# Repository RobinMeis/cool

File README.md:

# cool
Attempt to make a stupid fridge-freezer a bit smarter and more energy efficient

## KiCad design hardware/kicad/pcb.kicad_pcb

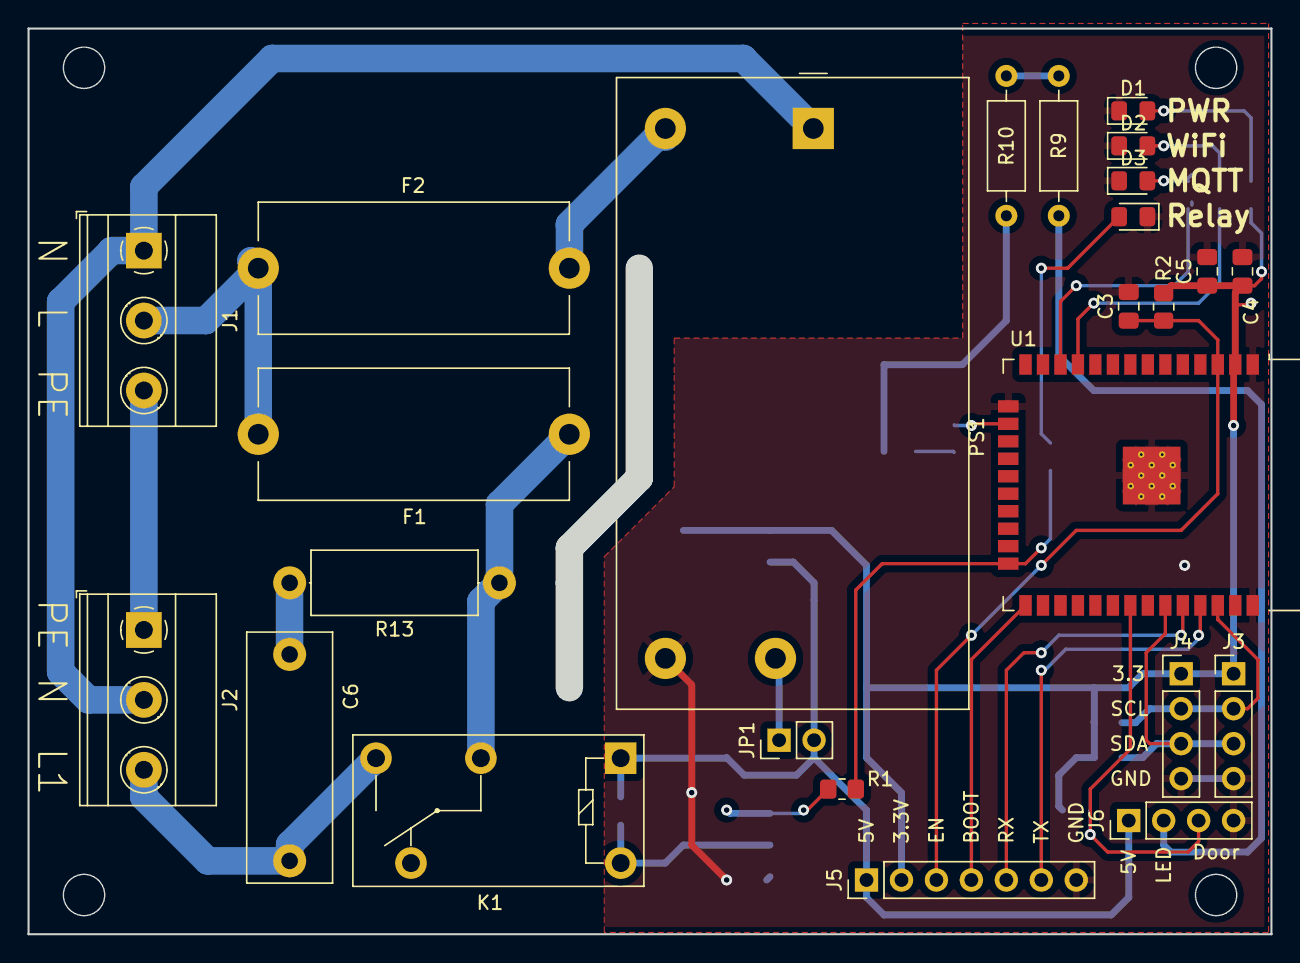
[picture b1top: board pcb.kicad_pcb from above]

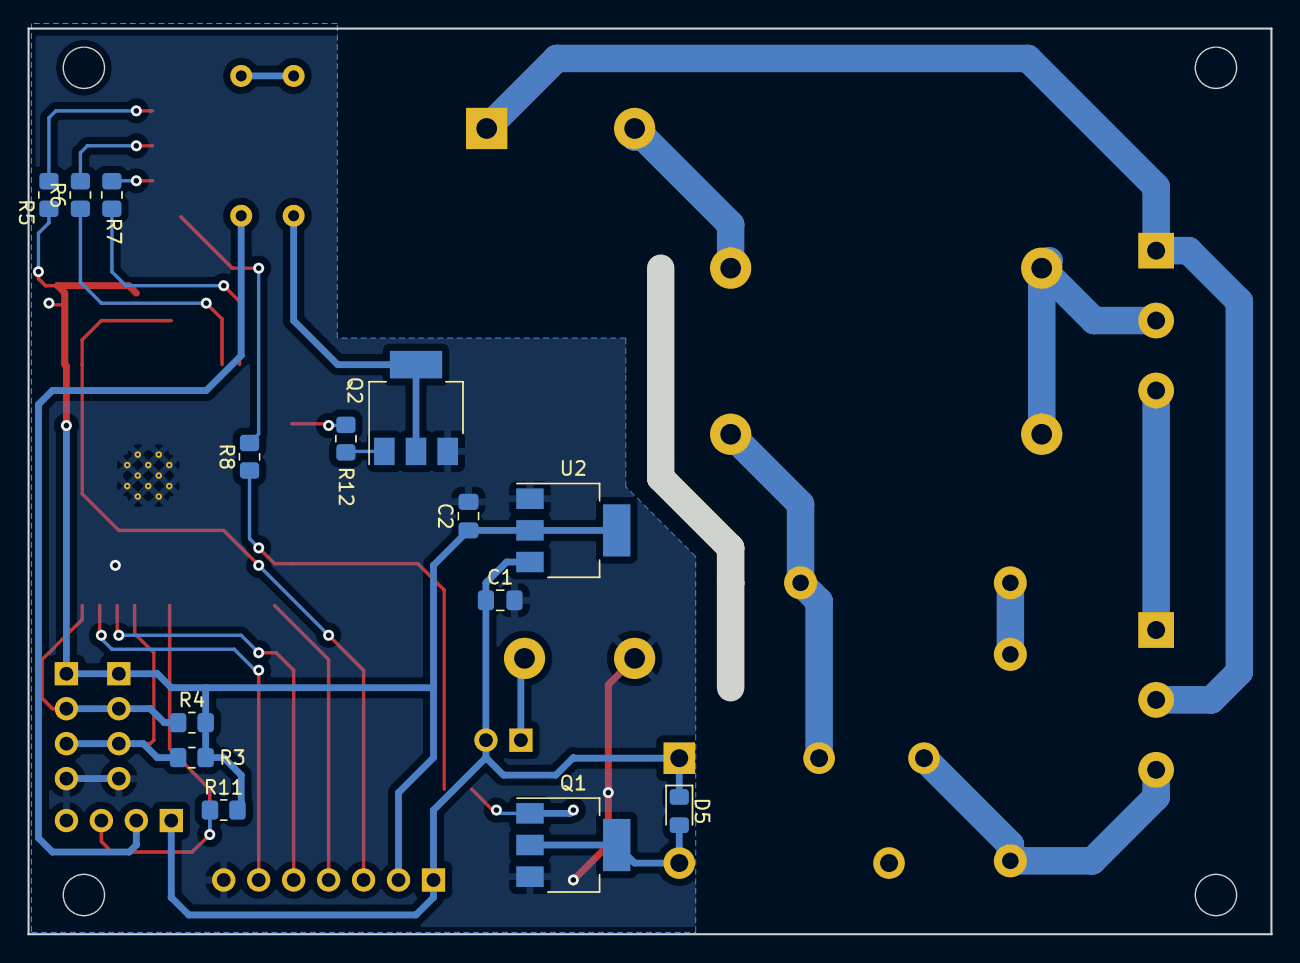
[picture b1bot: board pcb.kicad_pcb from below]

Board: 2 copper layers, 88.4 x 63.9 mm, 39 parts (14 on the bottom side), 32 nets.

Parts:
C1, C2: 22 uF; C_0805_2012Metric_Pad1.18x1.45mm_HandSolder
C3, C5: 100 nF; C_0805_2012Metric_Pad1.18x1.45mm_HandSolder
C4: 100 uF; C_0805_2012Metric_Pad1.18x1.45mm_HandSolder
C6: 100 nF; C_Rect_L18.0mm_W6.0mm_P15.00mm_FKS3_FKP3
D1, D2, D3, D4: LED; LED_0805_2012Metric_Pad1.15x1.40mm_HandSolder
D5: D; D_0805_2012Metric_Pad1.15x1.40mm_HandSolder
F1, F2: Fuse; Fuseholder_Cylinder-5x20mm_Stelvio-Kontek_PTF78_Horizontal_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
J1, J2: Screw_Terminal_01x03; TerminalBlock_Phoenix_MKDS-1,5-3-5.08_1x03_P5.08mm_Horizont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
J3, J4, J6: Conn_01x04_Male; PinHeader_1x04_P2.54mm_Vertical
J5: Conn_01x07_Male; PinHeader_1x07_P2.54mm_Vertical
JP1: Jumper_2_Bridged; PinHeader_1x02_P2.54mm_Vertical
K1: G5Q-1; Relay_SPDT_Omron-G5Q-1
PS1: IRM-05-5; Converter_ACDC_MeanWell_IRM-05-xx_THT
Q1, Q2: BCP56; SOT-223-3_TabPin2
R1, R5, R6, R7, R8, R12: 1k; R_0805_2012Metric_Pad1.20x1.40mm_HandSolder
R2, R3, R4, R11: 10k; R_0805_2012Metric_Pad1.20x1.40mm_HandSolder
R9, R10: 15; R_Axial_DIN0207_L6.3mm_D2.5mm_P10.16mm_Horizontal
R13: 220; R_Axial_DIN0414_L11.9mm_D4.5mm_P15.24mm_Horizontal
U1: ESP32-WROOM-32D; ESP32-WROOM-32
U2: AMS1117-3.3; SOT-223-3_TabPin2

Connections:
+3.3V: C2.1, C4.1, C5.1, J3.1, J4.1, J5.2, R2.2, R3.2, R4.2, R5.1, R11.2, U1.2 (VDD), U2.2 (VO)
+5V: C1.1, D5.1 (K), J5.1, J6.1, JP1.2 (B), K1.1, U2.3 (VI)
AC: F1.2, F2.1, J1.2
BOOT: J5.4, U1.25 (IO0)
Door: J6.3, R11.1, U1.31 (IO19)
EN: C3.1, J5.3, R2.1, U1.3 (EN)
Earth: J1.1, J2.2, PS1.1 (AC/N)
Earth_Protective: J1.3, J2.1
GND: C1.2, C2.2, C3.2, C4.2, C5.2, D1.1 (K), D2.1 (K), D3.1 (K), D4.1 (K), J3.4, J4.4, J5.7, J6.4, PS1.3 (-Vo), Q1.3 (E), Q2.3 (E), U1.1 (GND), U1.15 (GND), U1.38 (GND), U1.39 (GND), U2.1 (GND)
LED_MQTT: R7.1, U1.12 (IO27)
LED_WIFI: R6.1, U1.11 (IO26)
Light: Q2.2 (C), R10.2
unnamed: C6.1, R13.2
unnamed: C6.2, J2.3, K1.3
unnamed: D1.2 (A), R5.2
unnamed: D2.2 (A), R6.2
unnamed: D3.2 (A), R7.2
unnamed: D4.2 (A), R8.2
unnamed: D5.2 (A), K1.5, Q1.2 (C)
unnamed: F1.1, K1.2, R13.1
unnamed: F2.2, PS1.2 (AC/L)
unnamed: J6.2, R9.1
unnamed: JP1.1 (A), PS1.4 (+Vo)
unnamed: Q1.1 (B), R1.2
unnamed: Q2.1 (B), R12.2
unnamed: R9.2, R10.1
unnamed: R12.1, U1.16 (IO13)
RX: J5.5, U1.34 (RXD0/IO3)
Relay: R1.1, R8.1, U1.24 (IO2)
SCL: J3.2, J4.2, R4.1, U1.36 (IO22)
SDA: J3.3, J4.3, R3.1, U1.33 (IO21)
TX: J5.6, U1.35 (TXD0/IO1)

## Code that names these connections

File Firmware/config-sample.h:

#ifndef CONFIG_H
#define CONFIG_H

// Offset of temperature sensors
#define OFFSET_FRIDGE 0
#define OFFSET_FREEZER 0

// Wifi configuration
#define WIFI_SSID "IoT"
#define WIFI_PASSWORD "12345678"

// MQTT configuration
#define MQTT_SERVER "mqtt.local"
#define MQTT_PORT 1883
#define MQTT_CLIENT_ID host_name.c_str()
#define MQTT_USERNAME "user"
#define MQTT_PASSWORD "password"

// HTTP update server
#define HTTP_UPDATE_ENABLED true
#define HTTP_UPDATE_USERNAME "admin"
#define HTTP_UPDATE_PASSWORD "admin"

// Device type
#define HAS_FRIDGE true
#define HAS_FREEZER true

// Device name (autogenerated from device type)
#if HAS_FRIDGE==true
  #define DEVICE_NAME "Fridge"
#else
  #define DEVICE_NAME "Freezer"
#endif

// Pins
#define PIN_COMPRESSOR 2
#define PIN_LIGHT 13
#define PIN_DOOR 19
#define PIN_DOOR_ACTIVE_LOW true
#define DOOR_DEBOUNCE_TIME 200
#define LED_WIFI 26
#define LED_MQTT 27

// I2C addresses
#define I2C_ADDRESS_FRIDGE 0x76
#define I2C_ADDRESS_FREEZER 0x77

// Temperatures
#define FRIDGE_HVAC_MINIMUM 1
#define FRIDGE_HVAC_MAXIMUM 20
#define FREEZER_HVAC_MINIMUM -40
#define FREEZER_HVAC_MAXIMUM 0

// Default temperatures
#define FRIDGE_MINIMUM_DEFAULT 4
#define FRIDGE_MAXIMUM_DEFAULT 7
#define FREEZER_MINIMUM_DEFAULT -27
#define FREEZER_MAXIMUM_DEFAULT -4.5

// Temperatures for default mode
#define FRIDGE_MINIMUM 4
#define FRIDGE_MAXIMUM 7
#define FREEZER_MINIMUM -27
#define FREEZER_MAXIMUM -4.5

#endif

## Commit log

2023-02-24 Add kicad-backups
2023-02-24 Initial PCB
2023-02-24 Add config.h
2023-02-24 Add Python
2023-02-25 Allow longer duration for preset mode
2023-02-26 Increase maximum mode duration to 3 hours
2023-02-27 Rename directory
2023-02-27 Set maximum preset mode duration to 6 hours
2023-02-27 Remove auto boost stop
2023-02-27 Rename
2023-02-27 Swap priority to ensure cooling if at least one are is too warm
2023-02-28 Set retain flag
2023-03-05 Remove startup delay
2023-03-05 Add status LEDs
2023-03-05 Fix door debounce
2023-03-06 Fix typo
2023-03-06 Disable boost mode when lower limit has been reached
2023-03-09 Change hostname
2023-03-09 Change MQTT topics
2023-03-09 Generate unique entity IDs based on mac address
2023-03-09 Set entity category for config entities
2023-03-09 Add diagnostics
2023-03-09 Ignore .bin files
2023-03-09 Web updater
2023-03-10 Remove mqtt witch for updater
2023-03-10 Require password for web updater
2023-03-10 Use retain flag to set availability
2023-03-10 Rename mqtt_callback
2023-03-10 Remove homeassistant autodiscovery interval
2023-03-10 Remove old updater mqtt topics
2023-03-10 Update config sample for PCB
2023-03-10 Fix switch-off bug on fridge/freezer only devices
2023-03-10 Fix light range
